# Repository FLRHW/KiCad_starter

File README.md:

# FLRHW KiCad Starter

A KiCad 10 project template with hierarchical schematic examples, drawing
worksheets, and GitHub Actions automation using KiBot.

Start a project in KiCad, develop the design, and push changes to GitHub. CI
generates documentation and manufacturing files and commits them back to the
same branch. Retrieve the results with `git pull`.

Repository: [FLRHW/KiCad_starter](https://github.com/FLRHW/KiCad_starter).

Example project: [Desk_controller](https://github.com/FLRHW/Desk_controller),
a project created from this template, with generated documentation and
manufacturing outputs.

## Requirements

- KiCad 10 installed locally, with its standard symbol and footprint libraries.
- Python 3 to run the project setup and optional local utilities.
- Git and a GitHub account for the CI workflow.
- A browser and PDF viewer to inspect generated documents.

Docker and KiBot do not need to be installed locally. The build steps run in one digest-pinned Docker container on
a GitHub-hosted Ubuntu runner. Local KiCad and CI KiCad patch versions can differ;
the CI build report records the version that generated the outputs.

**Tested versions:** Local project creation and editing have been tested with
**KiCad 10.0.6 on Linux**. The pinned CI image uses **KiBot 1.9.1** and
**KiCad 10.0.5**. These are the tested versions, rather than a requirement that
local and CI KiCad patch versions match. Each run records its CI tool versions
in `output/reports/build-info.txt`.

**Platform testing:** This template has been tested only on Linux. Local project
creation and setup are expected to work on Windows with KiCad 10, Python 3 and Git,
but have not yet been verified there. The CI workflow runs on Ubuntu regardless
of the operating system used locally. Shell examples below use Linux syntax unless
stated otherwise.

## Included outputs

Depending on the configuration toggles, CI generates:

- ERC and DRC reports, including machine-readable JSON.
- Schematic PDF.
- Fabrication PDF with requirements, stackup and drill documentation.
- Assembly PDF with drawings, component counts and paginated BOM appendices.
- Separate top/bottom testpoint drawing pages.
- Gerber and Excellon drill files.
- CSV and XLSX BOMs and an interactive HTML BOM.
- Top/bottom pick-and-place CSV files.
- A STEP assembly and optional Blender renders, including bare-board views.
- An HTML index linking the generated outputs.
- Optional fabrication/assembly ZIP packages and revision comparison PDFs.

## Install the KiCad template

**Option A - Use your existing KiCad user-template folder**

1. In KiCad, open **Preferences → Configure Paths** and find
   `KICAD_USER_TEMPLATE_DIR`. If it is unset, use Option B.

2. Clone the repository inside that directory:

   ```bash
   cd "/path/to/your/KiCad/user/templates"
   git clone https://github.com/FLRHW/KiCad_starter.git
   ```

**Option B - Use a dedicated user templates folder**

1. Clone this repository into a folder under your user template
   directory. For example, on Linux:

   ```bash
   mkdir -p "$HOME/KiCadTemplates"
   git clone https://github.com/FLRHW/KiCad_starter.git "$HOME/KiCadTemplates/KiCad_starter"
   ```

2. In the KiCad Project Manager, open **Preferences → Configure Paths** and set
   `KICAD_USER_TEMPLATE_DIR` to the parent folder, such as
   `/home/your-user/KiCadTemplates`. Leave the system template path unchanged.

`meta/info.html` and `meta/icon.png` provide the template description and icon.
The `templates/` folder contains drawing worksheets; it is a different folder
from the directory used to install project templates.

## Create a new project and set it up

1. In KiCad choose **File → New Project…** and select **FLRHW KiCad Starter**.

2. Choose the new project name and location. KiCad renames the root project,
   schematic, PCB and rules files; the example child-sheet filenames remain
   unchanged.

3. **Do not yet open the schematic or PCB editors.** Open a terminal in the new
   project's root folder and run:

   ```bash
   python3 scripts/setup_project.py
   ```

   On Windows, `py scripts/setup_project.py` may be used instead.
   Keep the schematic and PCB editors closed while running setup. If they were
   opened and saved beforehand, the script may detect both old and new
   project-instance records and stop for review.

4. Open the new `.kicad_pro` file, check the hierarchy, save the design and run
   local ERC/DRC. The example hierarchy includes a cover page, system overview,
   block diagram, interface example and two circuit examples. Adapt or delete the
   examples through KiCad before removing their unused files from disk.

The setup script updates internal project-name records and installs the workflow
from `ci/workflows/` into `.github/workflows/`. This is required because KiCad
does not copy the hidden `.github/` folder when creating a project from a template.
Running setup again is safe when the files already match. It refuses to overwrite
a different existing workflow unless you explicitly use `--force`.

The workflow expects exactly one `.kicad_pcb` in the project root and a matching
root `.kicad_sch`. Hierarchical child sheets are supported.

## Connect the project to GitHub

Create an empty GitHub repository without adding another README, licence or
`.gitignore`. From the new project's root:

```bash
git init -b main
git remote add origin git@github.com:YOUR_ACCOUNT/YOUR_REPOSITORY.git
git add .
git commit -m "Create project from FLRHW KiCad Starter"
git push -u origin main
```

Replace the remote with your repository address.
If Actions is disabled for the repository, enable it. Repository or organisation
policies must permit the workflow's `contents: write` permission so CI can commit
generated outputs.

After a successful run:

```bash
git pull --ff-only
```

CI adds commits to the branch you pushed. Pull those commits before starting the
next edit. If a push is rejected because CI has added a commit and your local
changes are already committed, integrate it with `git pull --rebase`, resolve any
conflicts, and then push. Do not force-push over CI's output commits.

## Project settings and worksheets

- Set your project name, revision, company and issue date in the appropriate
  KiCad page settings and project text variables.
- Enter dates as `YYYY-MM-DD`; KiBot formats them for the documents.
- The BOM configuration reads **Manufacturer** and **Manufacturer Part Number**.
  Its displayed part-number column may be labelled **MPN**.
- Use KiCad's **Do not populate** flag for unfitted parts. Check BOM and
  pick-and-place filtering for your assembly requirements.
- Select the appropriate worksheet under `templates/` in schematic and PCB page
  settings. Board worksheets are supplied for A2/A3/A4/A5; schematic worksheets
  are supplied for A3/A4.
- CI updates the `SHEET_TITLE_n` text variables used by the contents page. The
  workflow commits the project file so these generated values can be pulled and
  displayed locally. Local values may remain stale until that update.

The supplied design rules, dimensions and fabrication notes are merely illustrative.
Set them to your board manufacturer's requirements and inspect the generated files
before ordering or assembling boards.

## Configuration toggles

Edit the `definitions:` document at the end of `config.kibot.yaml`:

| Setting | Values | Behaviour |
|---|---|---|
| `RENDER_MODE` | `disabled`, `low`, `mid`, `high` | Controls Blender rendering and image layers in drawings. |
| `ASSEMBLY_BOM_MODE` | `combined`, `fitted`, `separate`, `no bom` | Selects the assembly PDF's BOM appendices. |
| `ZIP_ENABLED` | `'true'`, `'false'` | Enables or disables manufacturing ZIP packages. |
| `DIFF_ENABLED` | `'true'`, `'false'` | Enables or disables revision comparisons. |
| `DIFF_BASE_REF` | Git commit or tag | Reference revision for comparisons. |

In `combined` mode, fitted and DNP parts share a table with a Status column.
`fitted` includes fitted parts only. `separate` creates distinct fitted and DNP
sections. Both omit Status because their section headings identify the population.
`no bom` omits the appendices. Source CSVs retain Status for classification.

Disabling renders leaves the PDF pages in place, with render areas blank and
associated image layers omitted. Higher render modes cost more CI time.

Several values use KiBot's `@DEFINITION@` substitution syntax. Keep the supplied
multi-document configuration structure; a generic YAML parser alone does not
perform these substitutions.

### Blender lighting

Define lights in `config.kibot.yaml`. The Blender hook in
`scripts/configure_blender_materials.py` then adjusts every AREA light,
including any additional ones you define.

The hook measures the rendered board and components, preserves each light's
direction from their centre, and aims the light toward that centre. It sets
the distance to six times the measured board size and the softbox width and
height to four times that size.

Consequently, moving a light farther along the same direction in the YAML
does not reduce its brightness: the script overrides that distance.

Light energy is handled separately:

- `energy: @AUTO_LIGHT_ENERGY@` uses board-size compensation calculated by
  the workflow.
- A numeric energy value remains fixed.
- Arithmetic expressions are not supported in the numeric energy field.

The distance and size adjustments apply to AREA lights, not SUN lights.
The current hook requires at least one AREA light when rendering is enabled.
It also adjusts materials and colour settings, so the final appearance is
controlled by both the YAML and the hook.

Use `RENDER_MODE` to disable rendering or select its quality. The hook is
designed for the pinned CI image; changing the KiBot or Blender version may
require checking its compatibility.

### Workflow dependencies and output selection

Use the supplied render, assembly BOM, ZIP and revision-comparison toggles
where possible. These are supported configuration paths; other outputs
cannot necessarily be removed or disabled independently.

Before changing an output's name, path or enabled state, check its references
in:

- `config.kibot.yaml`, including PDF images, tables and package definitions.
- The workflow's output-selection and exclusion lists.
- The helper scripts, especially `finalize_pdfs.py`.

Setting `run_by_default: false` only disables default execution. An output
may still be requested explicitly by another output or script. Removing its
definition can invalidate those requests and cause CI to fail.

Important dependencies:

- PDF finalisation requires the assembly PDF and both ERC/DRC JSON reports.
- Unless `ASSEMBLY_BOM_MODE` is `no bom`, it also requires the top and bottom
  assembly BOM CSVs under `output/tables/`. Keep their configured columns,
  including Status, even when Status is omitted from the PDF.
- The assembly cover-page iBOM link requires the generated iBOM HTML.
  Its current implementation expects an unmirrored first page at 1:1 scale
  and the named `assembly_ibom_link` group.
- ERC failures require the schematic PDF for its failure notice. DRC failures
  require the assembly and fabrication PDFs.
- Drawing tables, render placeholders and ZIP packages depend on their
  referenced outputs or files.

The workflow can fail before PDF finalisation—for example, when a required
configuration file is missing, project-file detection fails, a helper command
fails, or KiBot cannot resolve a referenced output. Its shell uses `set -e`,
so an unsuccessful command normally stops the current step.

Preserve the execution order: generate fresh outputs, finalise the PDFs,
then generate packages and the HTML index. Do not repeatedly finalise an
already-finalised assembly PDF.

Disabling generation does not delete previously committed outputs. Older
files may remain available to scripts or links, so their presence does not
prove they were regenerated.

`pdf_mask_colours.py` reads physical solder-mask colours from the PCB stackup,
not the editor display theme. Missing or unsupported colours use its fallback.

Run `setup_project.py` locally after template creation. Rendering and PDF
processing run inside the CI container; ordinary local Python does not
provide all their required dependencies.

## PCB document layers and placeholders

The PDF outputs use custom layers and named groups. Preserve them when clearing
the example PCB, and adapt their placement to the board and paper size.

| Layer | Purpose |
|---|---|
| `AssemblyOverview` | Assembly cover-page renders and related annotations. |
| `AssemblyTop`, `AssemblyBottom` | Side-specific render/table placeholders. |
| `AssyDNPTop`, `AssyDNPBottom` | Generated DNP markings. |
| `FabricationRender` | Bare-board render placeholders. |
| `FabricationNotes` | Requirements text and stackup drawing. |
| `FabricationDrillMap` | Generated drill drawings. |
| `TestpointsTop`, `TestpointsBottom` | Testpoint annotations. |

Image groups use KiBot's `kibot_image_...` conventions; table groups use the
configured table names. Keep the existing names aligned with the YAML and scripts.
For bottom testpoint labels, verify text orientation in KiCad's flipped view and
check the page's `mirror_pcb_text` setting. Testpoint filtering currently recognises
references in the form `TP` followed by digits.

Most supplied PCB drawing pages use an explicit 1:1 scale. A larger worksheet does
not automatically resize the drawing; change the page scaling and its displayed
scale label together when needed.

## Optional online browsing with GitHub Pages

The workflow can publish the generated `output/` directory as a website. The
existing HTML index links to PDFs, renders, the interactive BOM and downloadable
manufacturing files. Output commits and normal CI artifacts remain enabled.

To enable publishing in a project repository:

1. Open **Settings → Pages** and select **GitHub Actions** as the build and
   deployment source.
2. Open **Settings → Secrets and variables → Actions → Variables** and create a
   **repository variable** named `ENABLE_GITHUB_PAGES` with the value `true`.
   Use a repository variable, not an environment variable or secret.
3. Start a fresh workflow run on the repository's default branch, or push a commit
   to that branch. Set the variable before starting the run.
4. Open the URL shown by the `deploy-pages` job after it succeeds. For a normal
   project repository, it is `https://OWNER.github.io/REPOSITORY/`.

Publishing is disabled when the variable is absent or has any value other than
`true`. Feature branches build normally but do not publish. If the
`github-pages` environment restricts deployment branches, allow the repository's
default branch. No separate website repository or personal access token is needed.

The root `https://OWNER.github.io/` address does not need to exist for a project
website to work. The generated index determines the site's appearance; GitHub
Pages hosts those files without redesigning them.

Everything inside `output/` is published, including reports and build information.
Review those files before enabling publishing. For public repositories, treat the
website as public. Keep the HTML-index output enabled when publishing.

Example: [Desk_controller generated documentation](https://flrhw.github.io/Desk_controller/).

## Output locations and viewing

| Location | Contents |
|---|---|
| `output/` | Schematic PDF and root HTML index link. |
| `output/assembly/` | Assembly and testpoint PDFs, BOM/iBOM and placement files. |
| `output/fabrication/` | Fabrication PDF, Gerbers and drill files. |
| `output/3d/` | STEP model and enabled renders. |
| `output/tables/` | Auxiliary CSV tables used by the documents. |
| `output/reports/` | ERC/DRC reports, check status, build information and HTML navigation. |
| `output/packages/` | Enabled manufacturing ZIPs. |

Generated outputs are intentionally tracked in project repositories. Keep
`output/` out of their `.gitignore`. Remove generated outputs from the starter
before distributing it or creating new projects.

In the starter repository itself, CI uploads generated outputs as artifacts but
does not commit them, identified by the presence of `meta/info.html`. Projects
created through KiCad omit `meta/`, so their CI commits outputs normally.

Open `output/index.html` to browse generated files.

The standalone iBOM can normally be opened directly. Relative links from PDFs
depend on preserving the output folder layout and the PDF viewer's support for
opening local links.

ERC errors mark the schematic PDF; DRC errors mark the assembly and fabrication
PDFs. The workflow can continue generating documents after those design-check
errors. A green workflow therefore does not establish that the design checks passed:
inspect `output/reports/check-status.txt` and the ERC/DRC reports.

## Libraries, fonts and reproducibility

The starter uses standard KiCad libraries. Project-specific registrations with the
same nickname override global libraries, so avoid activating a partial snapshot while
you still need access to the complete installed library.

`scripts/clone_libs.py --help` describes the optional library snapshot utility.
For production projects, retain the required libraries and 3D models locally and
review the resulting library tables. Project-local models can be stored under
`lib/3D/` and referenced with `${KIPRJMOD}/lib/3D/...`.

Use fonts available in CI, such as DejaVu Sans, or explicitly provide suitable font
resources. Selecting a default font does not change text objects that explicitly
request another font. CI preferences and colours are stored under `ci/kicad/`.

The workflow pins its Docker image by digest and GitHub Actions by commit. The
tested image is mirrored under `ghcr.io/flrhw/kibot-kicad10`; preservation tooling
is maintained in [kicad10_ci_tools](https://github.com/FLRHW/kicad10_ci_tools).
The build report records the source commit, CI image and tool versions.

The hosted runner and missing-model downloads are separate dependencies.
A pinned digest fixes image contents but does not guarantee
that a registry will retain them forever. Keep a verified image archive outside the
registry for long-term recovery. Review external resources before freezing a release.

## Maintaining the template

- When maintaining the starter, edit `ci/workflows/kicad-environment.yml`, the
  workflow copy that KiCad includes in new projects. Then run
  `python3 scripts/setup_project.py --force` to update the active copy under
  `.github/workflows/`, and commit both files. GitHub executes the active copy.
  In a project created from the template, you can edit its active workflow
  directly; changes there do not update the starter or other projects.
- Keep both workflow exclusion lists in sync when adding outputs. Main outputs
  run before PDF finalisation; packages and the HTML index run afterwards.
- Changes to scripts, worksheets and YAML affect the template and future projects.
  Existing projects do not automatically inherit updates.
- Validate changes by creating a project with a different name and checking local
  ERC/DRC, CI, generated PDFs, links and output paths.
- Update this README when configuration names, paths or requirements change.
- In a generated project, replace this README with project documentation or move
  it to a retained template-usage guide.

## Licence

The original FLRHW KiCad Starter material—including its scripts, configuration,
worksheets, documentation and original example designs—is licensed under the
**MIT License**. See [LICENSE](LICENSE). Preserve the copyright and permission
notice when distributing copies or substantial portions of this material.

Using this template does not require your independently created hardware design
to use MIT. Choose and document the licence appropriate for your project. If you
replace a generated project's root licence, retain the template's MIT notice in a
clearly identified location, for example `LICENSES/FLRHW-KiCad-Starter-MIT.txt`, and
state which reused material it covers.

Third-party software, libraries, models, fonts and other incorporated material
retain their respective licences. The template's MIT licence does not relicense
them. Preserve applicable third-party copyright and licence notices, including
those accompanying generated outputs that contain third-party code, such as iBOM.

All product names and trademarks belong to their respective owners. References
are descriptive and do not imply endorsement or affiliation. The template is
provided as is, without warranty, under the terms of LICENSE.

## Credits and acknowledgements

Development of this template was AI assisted, including work on configuration,
helper scripts, documentation and troubleshooting. Project decisions and testing
were carried out by FLRHW.

This template relies on the work of many open-source contributors:

- [KiBot](https://github.com/INTI-CMNB/KiBot), developed by Salvador E. Tropea,
  INTI and contributors, building on work including John Beard's KiPlot:
  automation, reports, exports and document generation.
- [KDT_Hierarchical_KiBot](https://github.com/nguyen-v/KDT_Hierarchical_KiBot),
  by Vincent Nguyen: inspiration for project organisation and automated
  documentation.
- [KiCad](https://www.kicad.org/) and its library contributors: schematic/PCB
  editing, checks, plotting and 3D export.
- [KiAuto](https://github.com/INTI-CMNB/KiAuto): KiCad automation utilities.
- [InteractiveHtmlBom](https://github.com/openscopeproject/InteractiveHtmlBom),
  by qu1ck and contributors: interactive assembly BOM.
- [Blender](https://www.blender.org/) and
  [PCB2Blender](https://github.com/30350n/pcb2blender): board rendering.
- [GitHub Actions](https://github.com/features/actions) and its action authors:
  CI execution, checkout and artifact handling.

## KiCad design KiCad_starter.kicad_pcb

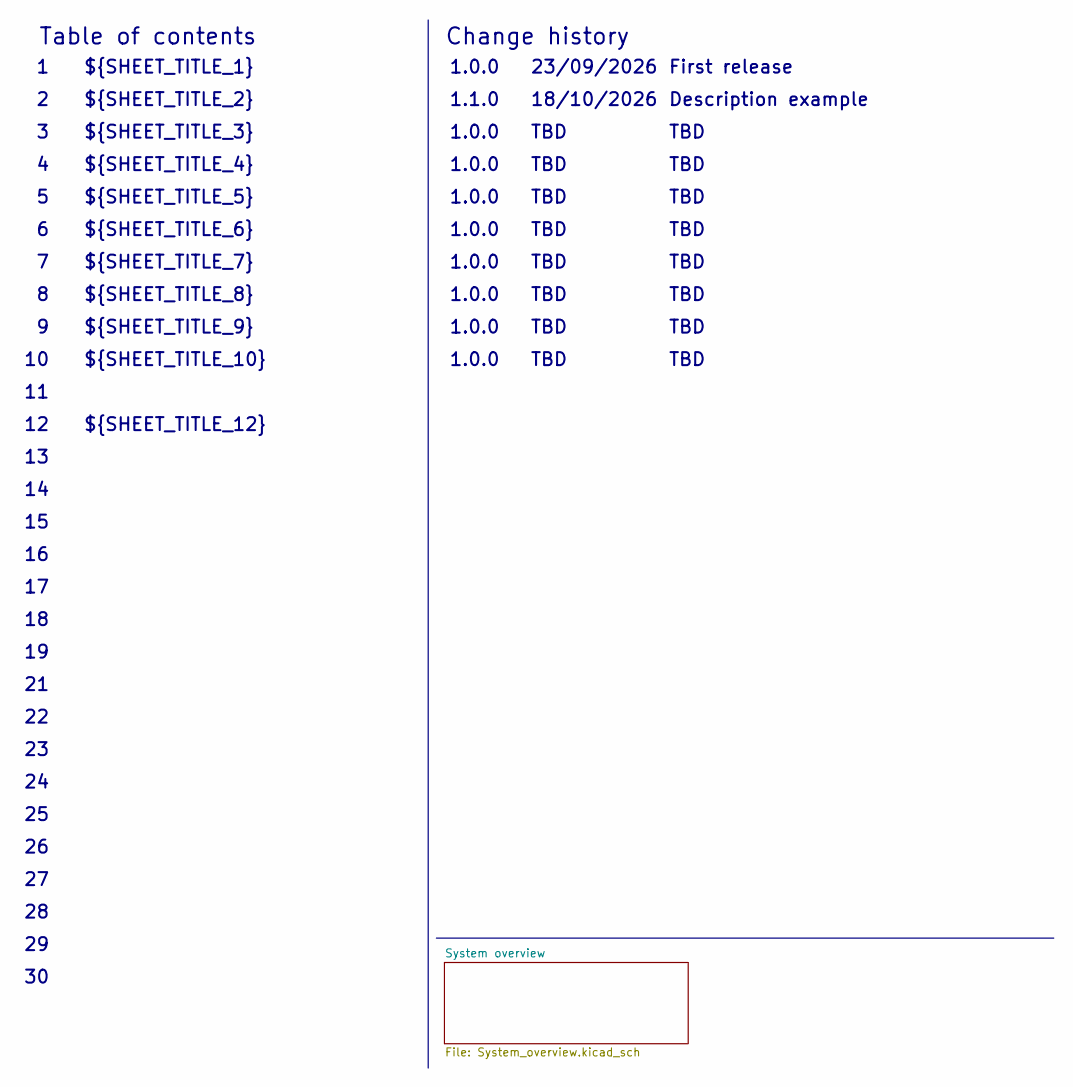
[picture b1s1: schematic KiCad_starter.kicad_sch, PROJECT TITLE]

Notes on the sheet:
Table of contents
1.0.0
TBD
Change history
First release
${SHEET_TITLE_1}
1.1.0
${SHEET_TITLE_7}
${SHEET_TITLE_8}
${SHEET_TITLE_3}
${SHEET_TITLE_9}
${SHEET_TITLE_5}
18/10/2026
${SHEET_TITLE_2}
${SHEET_TITLE_10}
${SHEET_TITLE_4}
${SHEET_TITLE_6}
23/09/2026
${SHEET_TITLE_12}
Description example

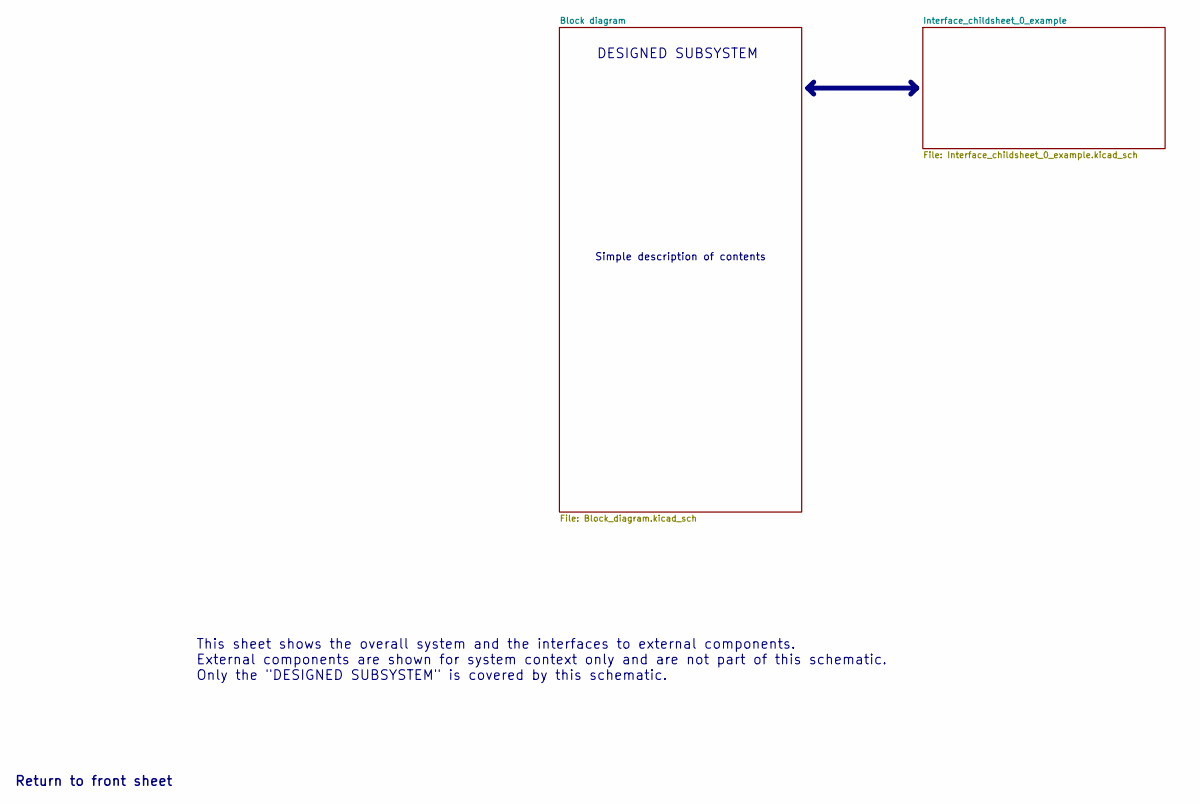
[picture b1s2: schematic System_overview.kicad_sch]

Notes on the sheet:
This sheet shows the overall system and the interfaces to external components. External components are shown for system context only and are not part of this schematic. Only the "DESIGNED SUBSYSTEM" is covered by this schematic.
Simple description of contents
DESIGNED SUBSYSTEM
Return to front sheet

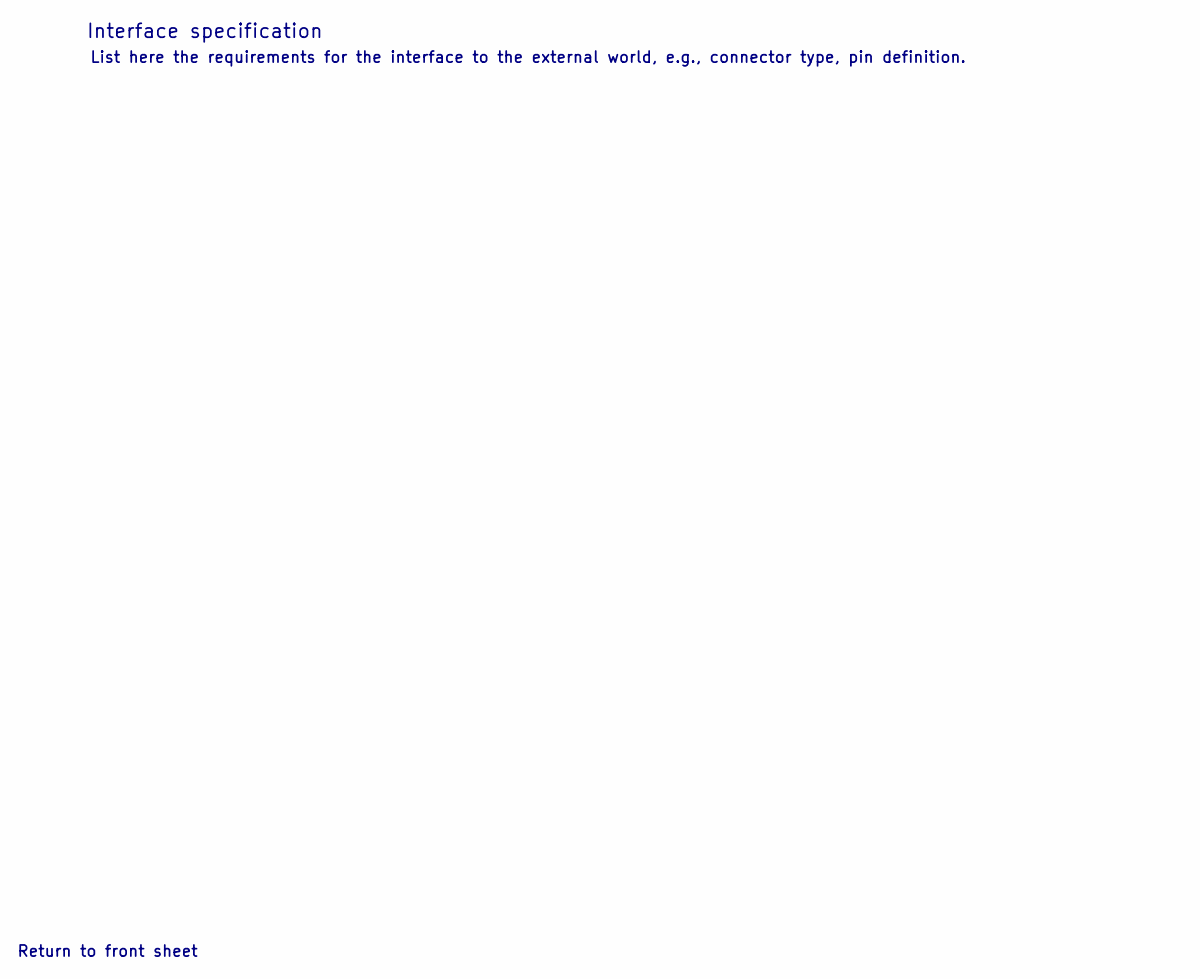
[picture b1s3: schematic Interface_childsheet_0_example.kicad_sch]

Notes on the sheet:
List here the requirements for the interface to the external world, e.g., connector type, pin definition.
Return to front sheet
Interface specification

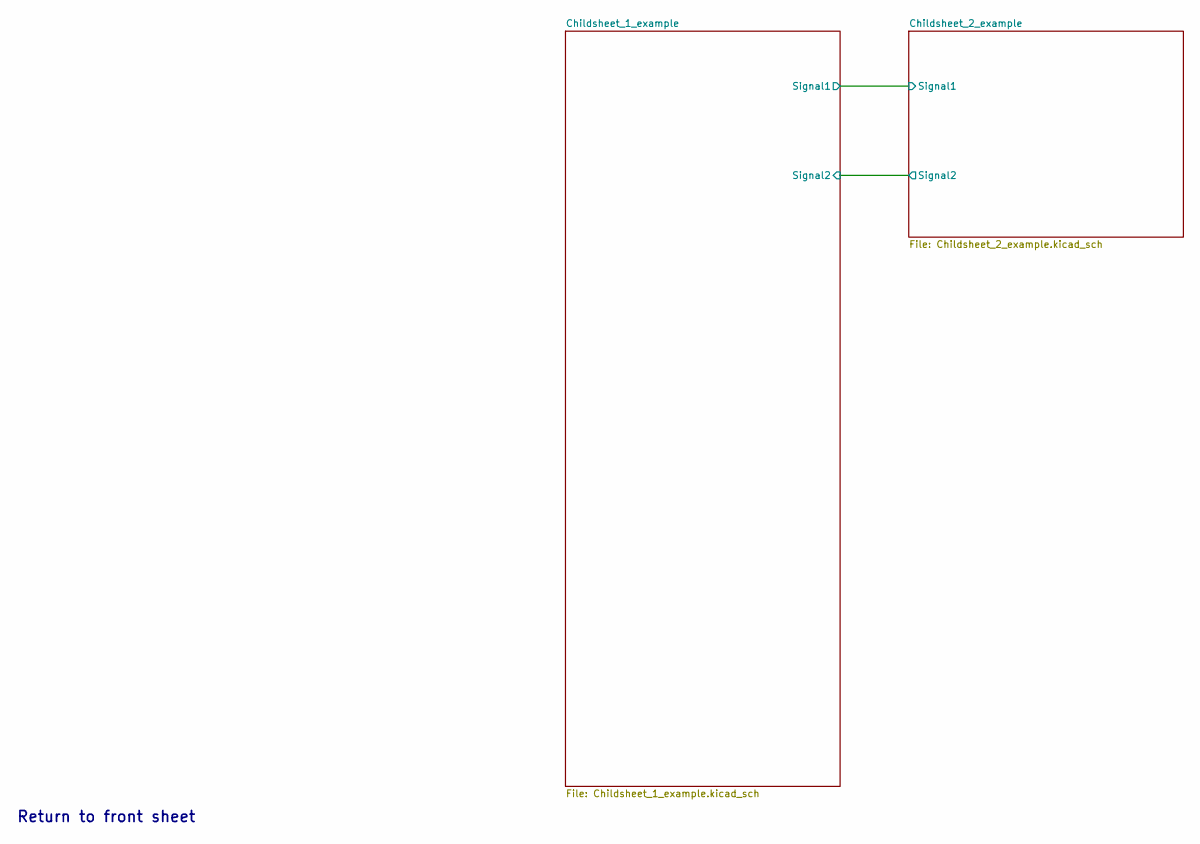
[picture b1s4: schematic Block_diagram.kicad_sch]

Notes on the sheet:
Return to front sheet

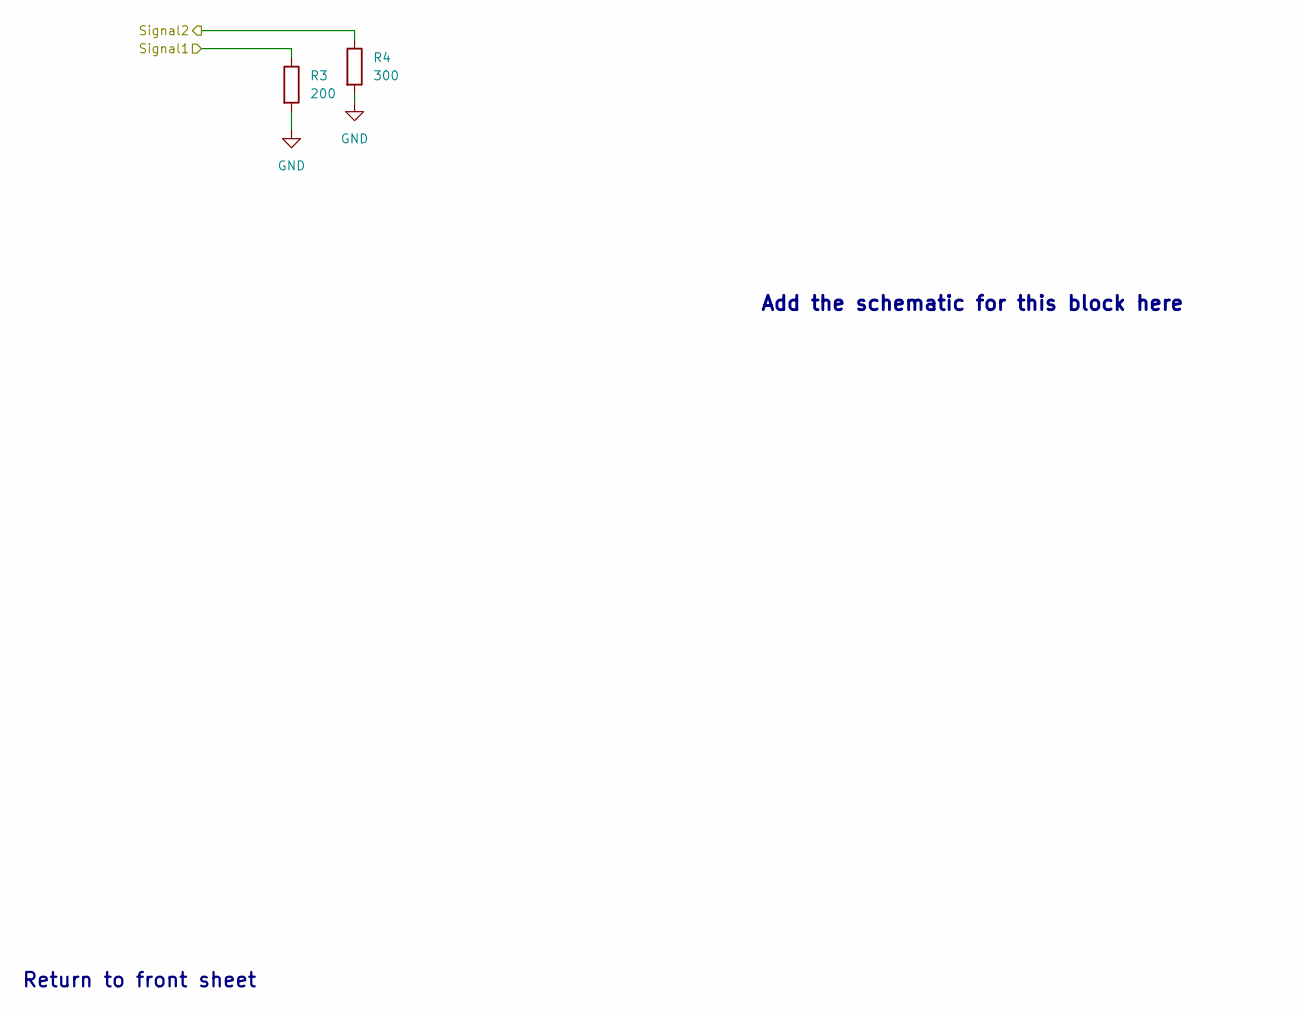
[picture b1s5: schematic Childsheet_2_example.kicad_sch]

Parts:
R3: 200; R_0603_1608Metric_Pad0.98x0.95mm_HandSolder; Manufacturer Part Number Example
R4: 300; R_0603_1608Metric_Pad0.98x0.95mm_HandSolder; Manufacturer Part Number Example

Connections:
/System overview/Block diagram/Childsheet_1_example/Signal1: R3.1; also elsewhere on the board
/System overview/Block diagram/Childsheet_1_example/Signal2: R4.1; also elsewhere on the board
GND: R3.2, R4.2; also elsewhere on the board

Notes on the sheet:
Add the schematic for this block here
Return to front sheet

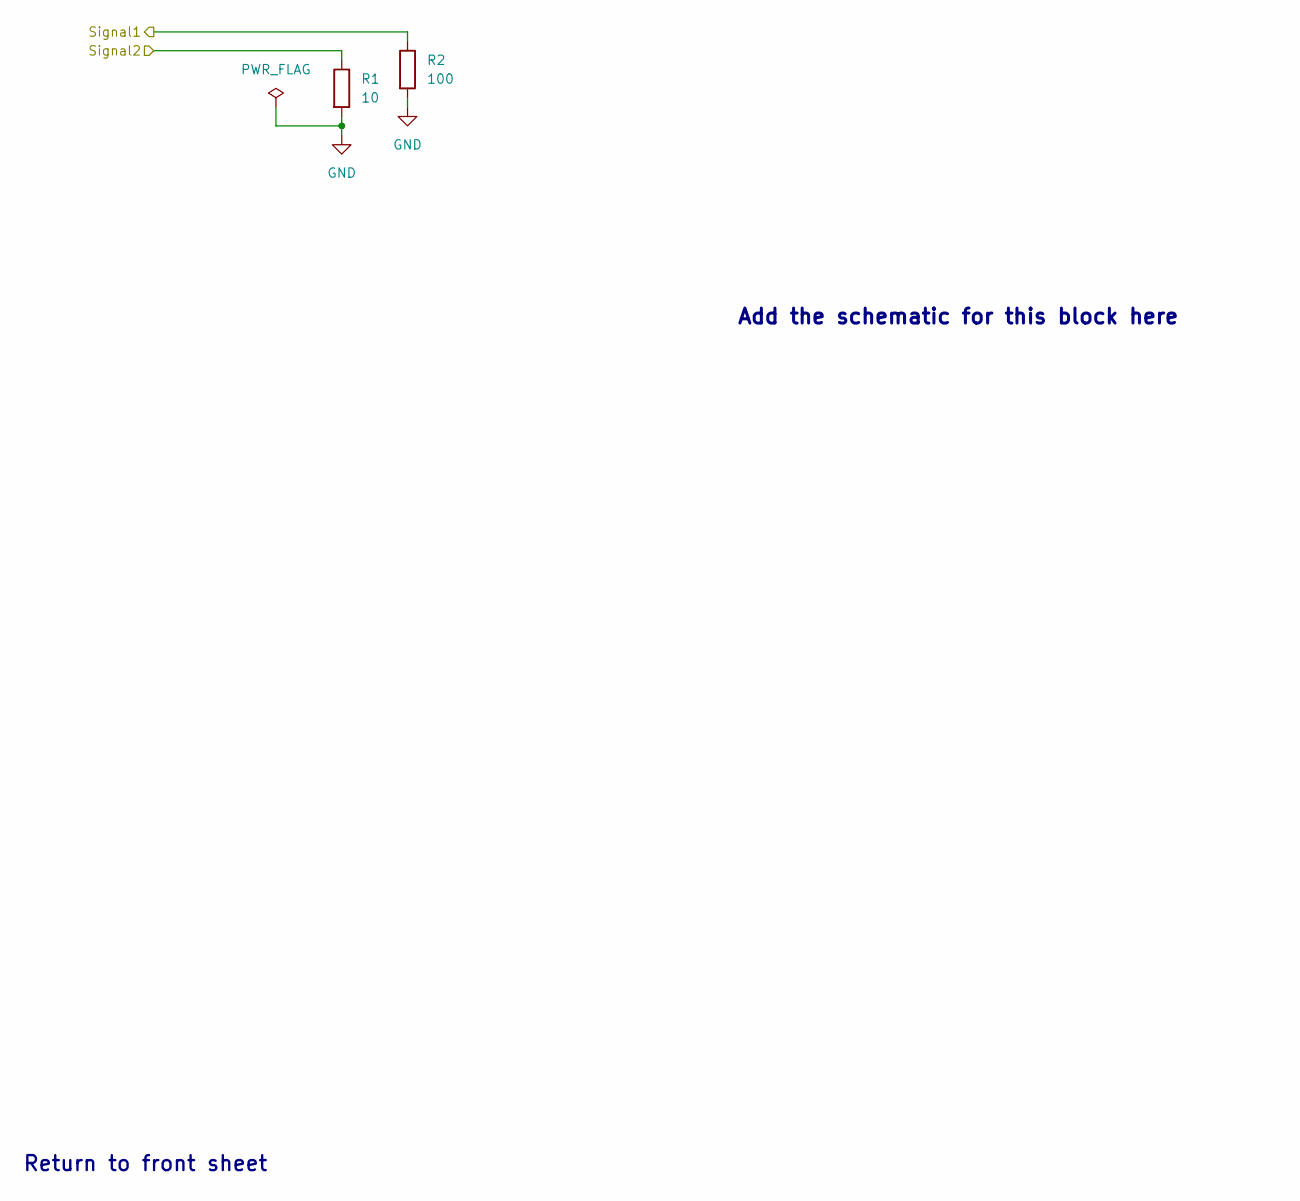
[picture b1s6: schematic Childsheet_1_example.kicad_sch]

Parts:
R1: 10; R_0603_1608Metric_Pad0.98x0.95mm_HandSolder; Manufacturer Part Number Example
R2: 100; R_0603_1608Metric_Pad0.98x0.95mm_HandSolder; Manufacturer Part Number Example

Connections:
/System overview/Block diagram/Childsheet_1_example/Signal1: R2.1; also elsewhere on the board
/System overview/Block diagram/Childsheet_1_example/Signal2: R1.1; also elsewhere on the board
GND: R1.2, R2.2; also elsewhere on the board

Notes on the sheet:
Add the schematic for this block here
Return to front sheet

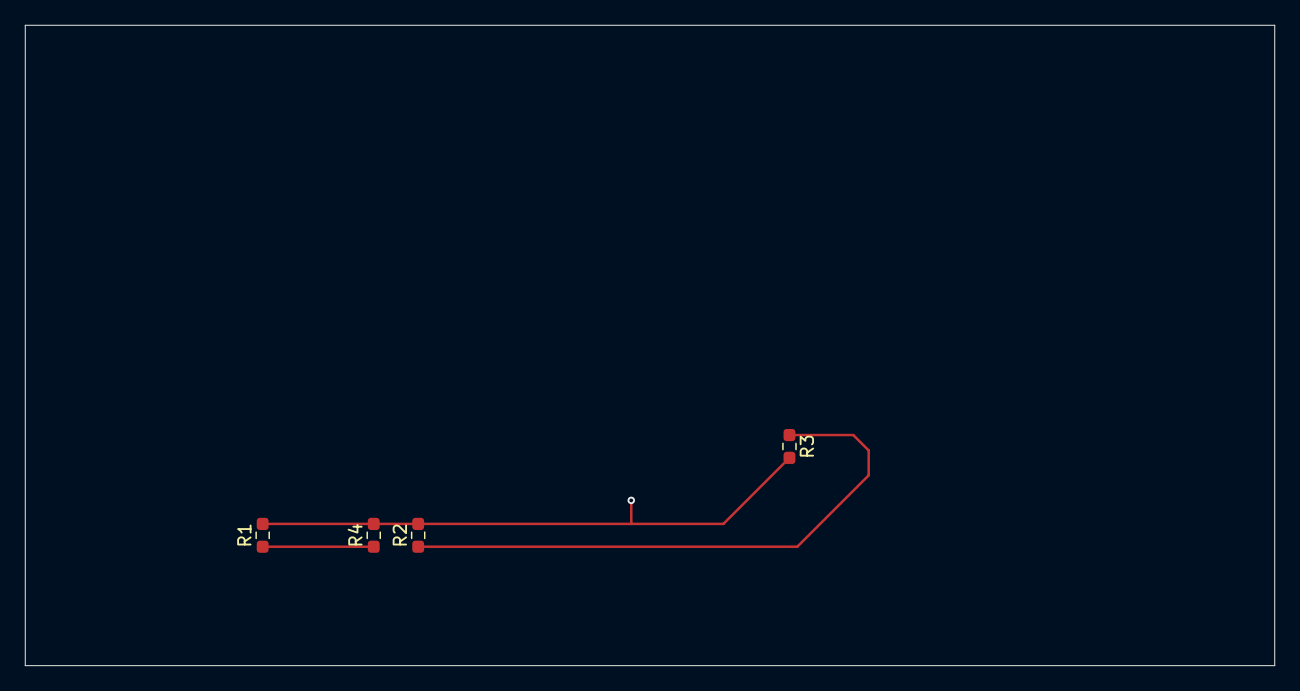
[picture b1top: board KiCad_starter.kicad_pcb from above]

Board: 2 copper layers, 100.0 x 51.2 mm, 4 parts (0 on the bottom side), 3 nets.
